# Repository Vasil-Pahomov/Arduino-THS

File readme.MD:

# General
This is Arduno-based air quality sensor and logger.
The following air quality parameters are measured:
- Temperature
- Humidity
- CO2 level
- total volatile organic compound (TVOC) level
- particle matter (dust) PM1.0, PM2.5 and PM10 levels

It can be powered either with batteries (I used 18560 recharge lithium) or with USB power supply.
The sensor stores data on MicroSD card and is able to download it to companion application with Bluetooth. An Android companion is designed: https://github.com/Vasil-Pahomov/AQS-Android or https://github.com/AlexeyKatsuro/ABTEx

# Circuit

# Part list

| Part | Image |
| ---- | ----- |
| Arduino Pro Mini (3.3V) |  |
| BME280 temperature and humidity sensor board |  |
| MH-Z19B CO2 sensor |  |
| CCS811 TVOC sensor board |  |
| PMS5003 dust sensor |  |
| Nokia 5110 LCD |  |
| HC-06 bluetooth board |  |
| TP4056 charger board |  |
| 5V boost converter |  |

# Log file format
Files are numbered starting from 0.log. Each file 10000 records. Record structure is defined in SDLog.h.
Once file numbers overcome 4000, it starts to delete files from the beginning.
Number of current file being written is stored in file named 'i' (2-byte unsigned word)

# Protocol format
## General
Organized as asyncronous messaging protocol. That is, both phone and sensor can send messages to each other. In fact, some messages resemble classis client-server communication.
## Message structure
| Field | Bytes | Description |
| ----- | ----- | ----------- |
| SGN | 2 | Signature=0xDEAF  |
| TYPE | 1 | Message type |
| DATA | ? | Message data, length depends on message type |

## Phone messages
### Sync time
TYPE=0x00
Sends current time to the sensor for sync up

| Field | Bytes | Description |
| ----- | ----- | ----------- |
| TIME | 4 | Unix timestamp |

### Read data
TYPE=0x01
Triggers sending data from the sensor

| Field | Bytes | Description |
| ----- | ----- | ----------- |
| FROMIDX | 4 | Index of starting record to read (including) |
| TOIDX | 4 | Index of ending record to read (including) |

### Reset storage
TYPE=0x02
Resets the storage (starts writing storage data anew)

The command has no body

### Calibrate CO2 sensor
TYPE=0x03
Sends calibration command to CO2 sensor. The sensor MUST be at least 20 minutes at open air environment (400 PPM).

The command has no body

## Sensor messages
### Status
TYPE=0x00

| Field | Bytes | Description |
| ----- | ----- | ----------- |
| STAT | 1 | Status:  0x00 if everything is OK, detailed see below |
| BAT | 1 | Battery percentage |
| LOGIDX | 4 | Number of last logged record (sequential, never overflows), returns 0xFFFFFFFF when there's SD card error |
| DATA | sizeof(Data) | Last sensor readings, Data structure (see Data.h) |

#### Status byte
Zero value means OK, one - failure

| Bit | Description |
| ----- | ----------- |
| 0 | BME sensor |
| 1 | MH-Z19 sensor |
| 2 | PMS5003 sensor |
| 3 | CCS811 sensor |
| 4 | SD card |
| 5 | Time was synchronized |
| 6 | RESERVED (always 0) |
| 7 | RESERVED (always 0) |

### Data
| Field | Bytes | Description |
| ----- | ----- | ----------- |
| FROMIDX | 4 | Index of starting record |
| TOIDX | 4 | Index of ending record (including) |
| DATA | sizeof(Data)*N | Data records, N=TOIDX-FROMIDX |

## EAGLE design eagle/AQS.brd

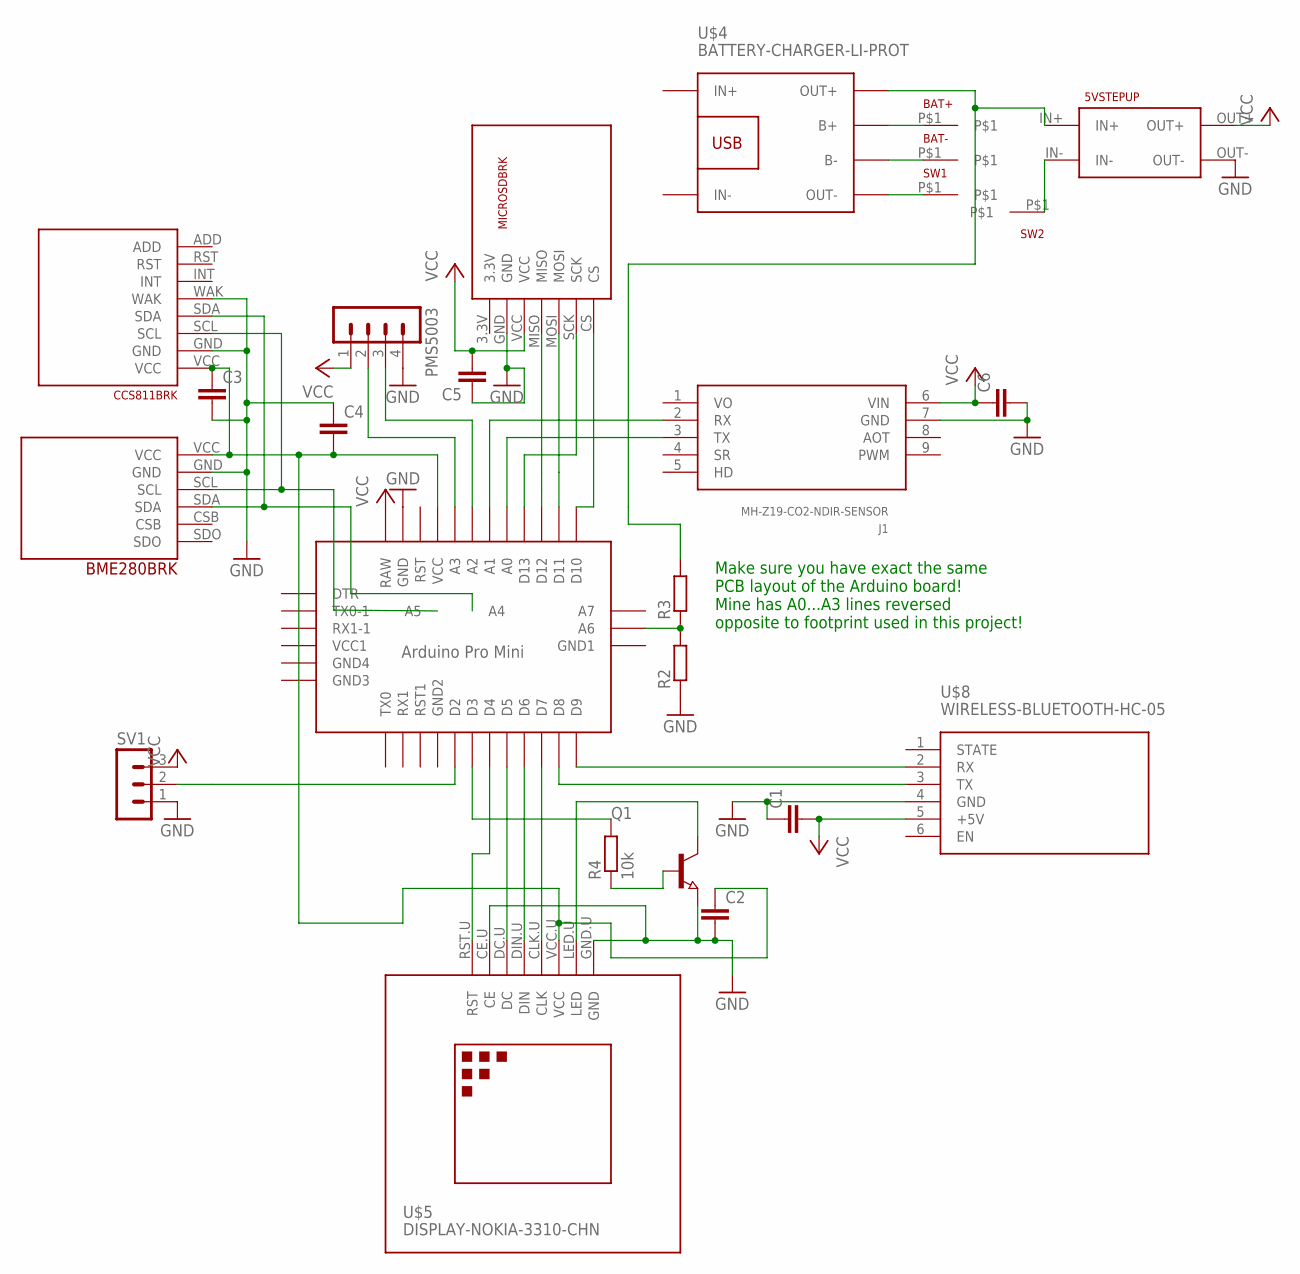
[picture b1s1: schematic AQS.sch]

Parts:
BAT+: PIN
BAT-: PIN
C1, C2, C3, C4, C5, C6: CC1206; C1206
J1: MH-Z19-CO2-NDIR-SENSOR; MH-Z19
PMS5003: MA04-1
Q1: NPN-TRANSISTOR_SOT23; SOT23
R2, R3: R-EU_0207/10; 0207/10
R4: 10k; 0207/10
SV1: MA03-1
SW1, SW2: PIN
U$1: ABK-PRO-MINI
U$2: BME280BRK
U$3: 5VSTEPUP
U$4: BATTERY-CHARGER-LI-PROT
U$5: DISPLAY-NOKIA-3310-CHN
U$6: CCS811BRK
U$7: MICROSDBRK
U$8: WIRELESS-BLUETOOTH-HC-05

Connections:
3.3V: U$7.3.3V
33V: C2.1, C3.1, C4.2, U$1.VCC, U$2.VCC, U$5.VCC.U (VCC), U$6.VCC
GND: C1.1, C2.2, C3.2, C4.1, C5.1, C6.2, J1.7 (GND), PMS5003.4, Q1.2 (E), R2.1, SV1.1, U$1.GND, U$2.GND, U$3.OUT-, U$5.CE.U (CE), U$5.GND.U (GND), U$6.GND, U$6.WAK, U$7.GND, U$8.4 (GND)
unnamed: BAT+.P$1, U$4.B+
unnamed: BAT-.P$1, U$4.B-
unnamed: R3.2, U$3.IN+, U$4.OUT+
unnamed: SW2.P$1, U$3.IN-
unnamed: U$1.A4, U$2.SDA, U$6.SDA
unnamed: U$1.A5, U$2.SCL, U$6.SCL
unnamed: U$1.D7, U$5.CLK.U (CLK)
unnamed: U$1.D6, U$5.DIN.U (DIN)
unnamed: U$1.D5, U$5.DC.U (DC)
unnamed: U$1.D4, U$5.RST.U (RST)
unnamed: Q1.3 (C), U$5.LED.U (LED)
unnamed: SW1.P$1, U$4.OUT-
unnamed: U$1.D9, U$8.2 (RX)
unnamed: U$1.D10, U$7.CS
unnamed: U$1.D11, U$7.MOSI
unnamed: U$1.D12, U$7.MISO
unnamed: U$1.D13, U$7.SCK
unnamed: J1.3 (TX), U$1.A0
unnamed: J1.2 (RX), U$1.A1
unnamed: U$1.D8, U$8.3 (TX)
unnamed: SV1.2, U$1.D2
unnamed: PMS5003.3, U$1.A2
unnamed: PMS5003.2, U$1.A3
unnamed: R2.2, R3.1, U$1.A6
unnamed: Q1.1 (B), R4.1
unnamed: R4.2, U$1.D3
VCC: C1.2, C5.2, C6.1, J1.6 (VIN), PMS5003.1, SV1.3, U$1.RAW, U$3.OUT+, U$7.VCC, U$8.5 (+5V)
VO: J1.1 (VO)

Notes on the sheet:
Make sure you have exact the same PCB layout of the Arduino board! Mine has A0...A3 lines reversed opposite to footprint used in this project!

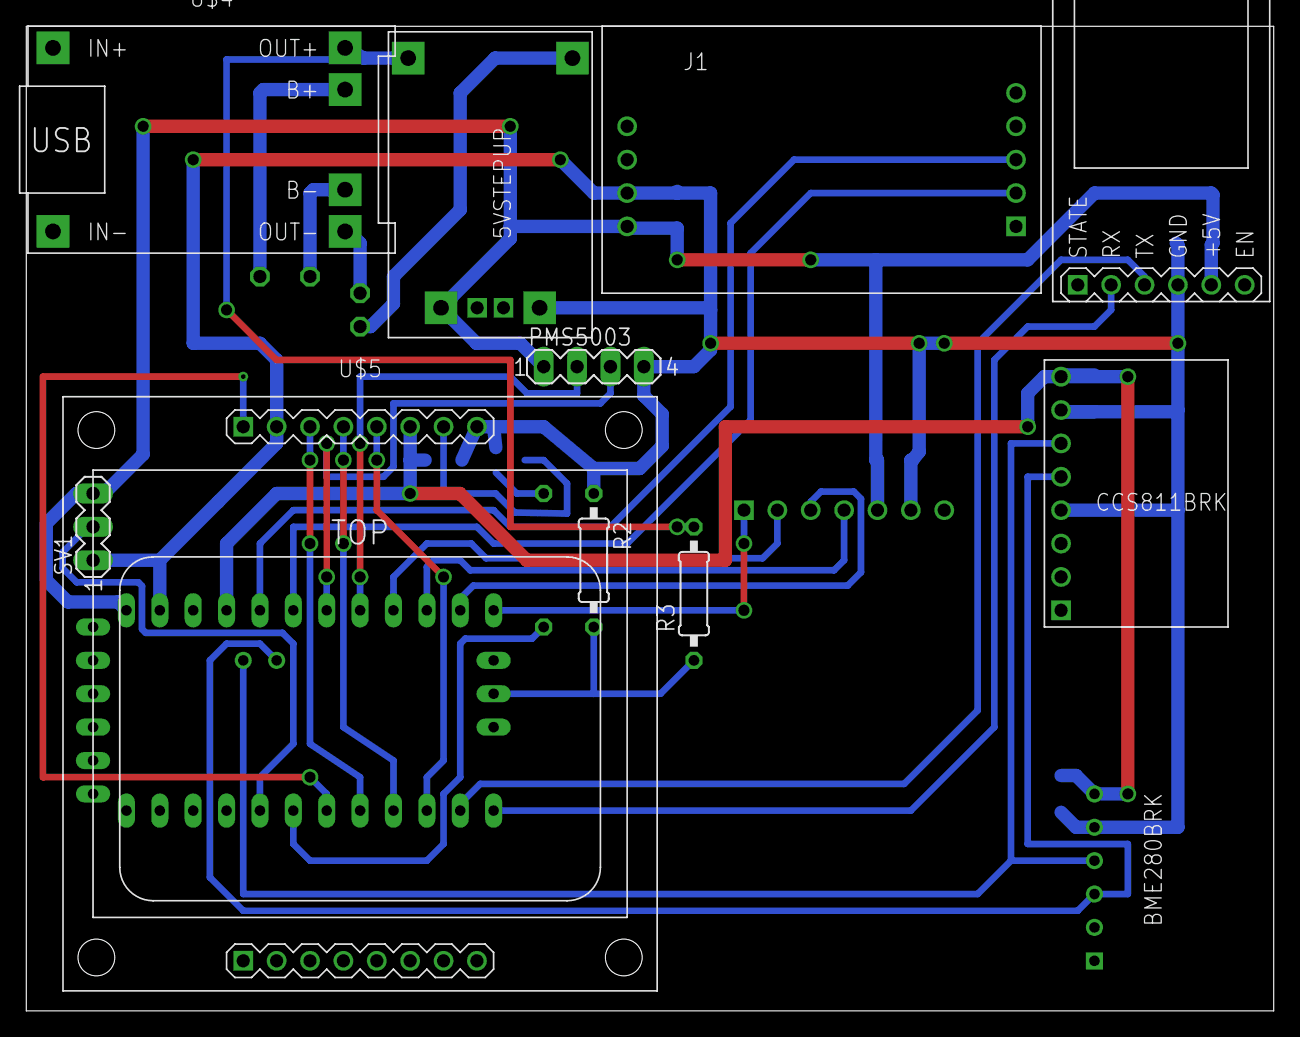
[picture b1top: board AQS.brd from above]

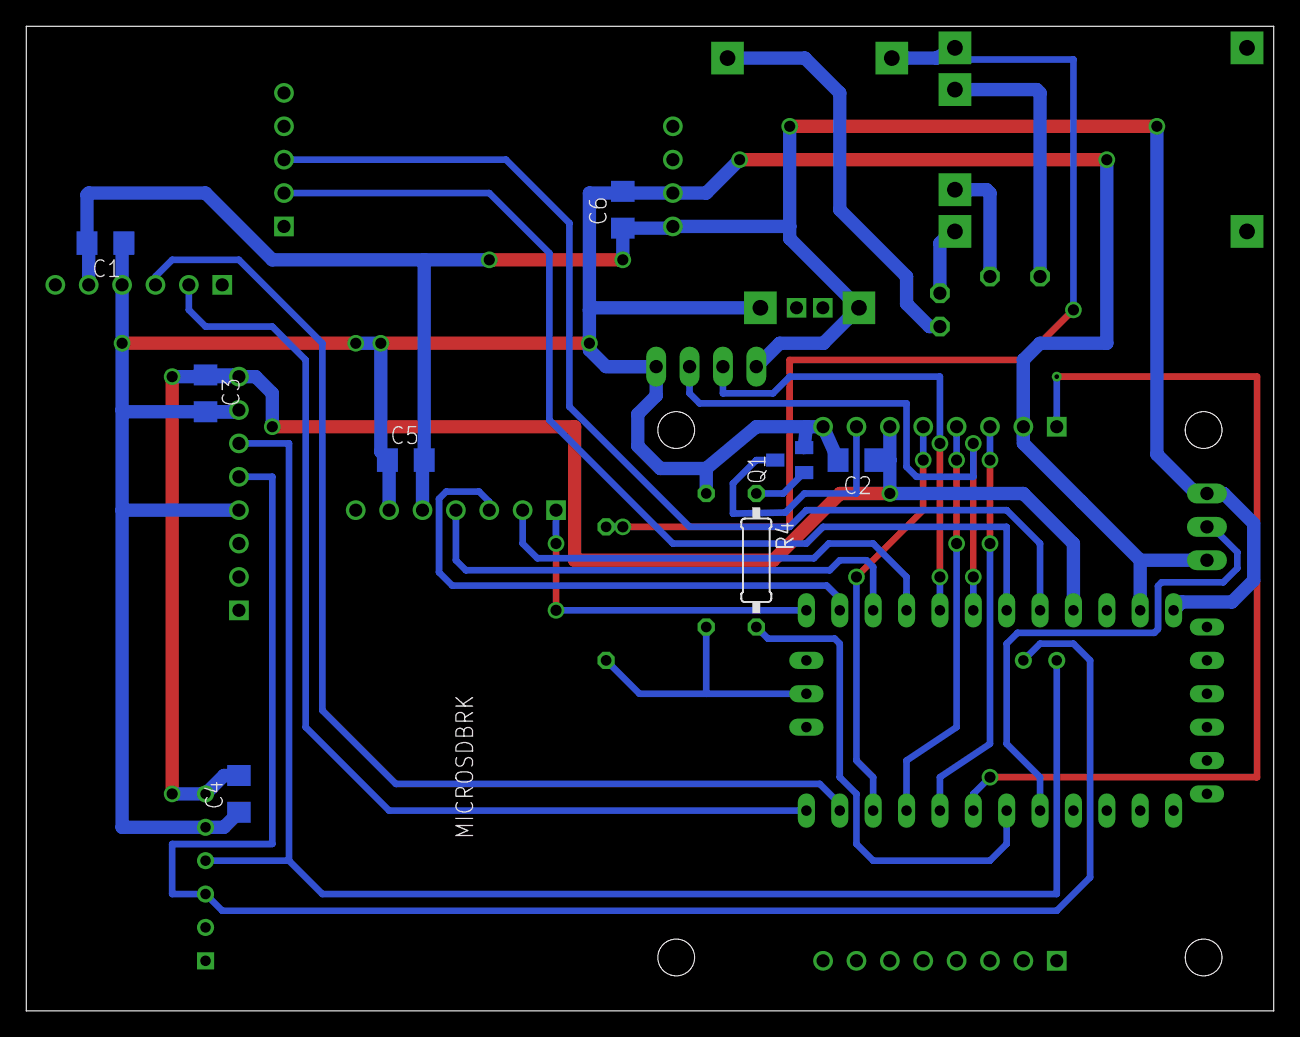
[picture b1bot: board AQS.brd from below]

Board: 2 copper layers, 94.9 x 74.9 mm, 25 parts (9 on the bottom side), 29 nets.

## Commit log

2018-04-03 added basic mh_z19 reading
2018-05-25 wokring with BMP280
2018-06-22 sample version with bme sensor
2018-09-04 Added support for PMS5003 sensor
2018-09-05 fixes and improvements to PMS5003
2018-09-05 added readme initial
2018-09-19 Added logging to SD card
2018-10-23 Added protocol (v0)
2018-10-24 Operational version with logging and beginning of BT protocol implementation. Some wiring changes for MH_Z19 and PMS5003 due to actual PCB layout
2019-01-23 Version sending status data over BT
2019-01-23 Readme update - the protocol
2019-01-24 Support for sync command
2019-01-25 Added reset storage cmd
2019-01-27 Zero version with transmit data support
2019-01-29 Fix data transfer, some refactoring Some fu..n magic is in SDLog.cpp, but it works
2019-01-29 Fix index file write (for some reason it wasn't overwritten but appended)
2019-01-29 Updated to 1000 records/file, fixed some warnings ...and this made BT receiving work again (the same WTF magic)
2019-02-06 Working data transmission with progress indication Increased measurement interval to 20 secs (avoid periodic TVOC drops at 10 sec)
2019-03-14 Added CO2 calibration command
2019-03-14 Added calibration command (at a cost of nice glyphs) Also removed LED handling that was already commented out
2019-03-14 Smart progress updating while uploading data (should improve upload performance) Force update readings after command is executed Some cleanup
2019-04-24 Multiple battery measurements averaged - more steady battery percentage readings
2019-04-29 Battery level tuned
2019-09-01 schematic image, eagle project files and libraries
2019-09-01 Part pics
2019-09-01 Pics follow-up
2019-09-01 Pics cleanup
2019-09-01 Image fix
2020-02-21 Fix wrong range reply when over 65565 records Add basic radiation support
2020-02-23 Updated radiation readings: sliding averaging, debouncing
2020-02-25 Reduced Heiger averaging queue length (seemed unstable on writing to SD card)
2020-03-27 Heiger - extend single measurement range to 1 min Some cosmetic changes
2021-06-11 Switch to PlatformIO + VS Code
2021-06-11 (follow-up)
2021-07-21 Disassembled not working code - trying to fit RTC module
2021-07-26 Replacing SoftareSerial with NeoSWSerial, remaking PMS5003 code and some more changes: 1. My PMS5003 has broken and does not respond to commands any more, so using default active mode (only listen). 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
2022-03-23 EMA filter for Heiger TinyBME280 to lower flash usage
